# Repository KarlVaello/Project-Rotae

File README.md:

# Project-Rotae
Bike Computer, based on arduino platform. This project involves hardware, software and project design.

TASK LIST
- [ ] Hardware - Peripherals board designs
- [ ] Peripherals - Code
- [ ] Peripherals - Document proces of bluetooth configuration
- [ ] Peripherals - Shut down peripherial power via detection bluetooth unconnected
- [ ] UI - Tactile
- [ ] Hardware - batteries
- [ ] GPS general functions
- [ ] GPS location stop detection (Time stops)
- [ ] SD, save time, gps track, and data

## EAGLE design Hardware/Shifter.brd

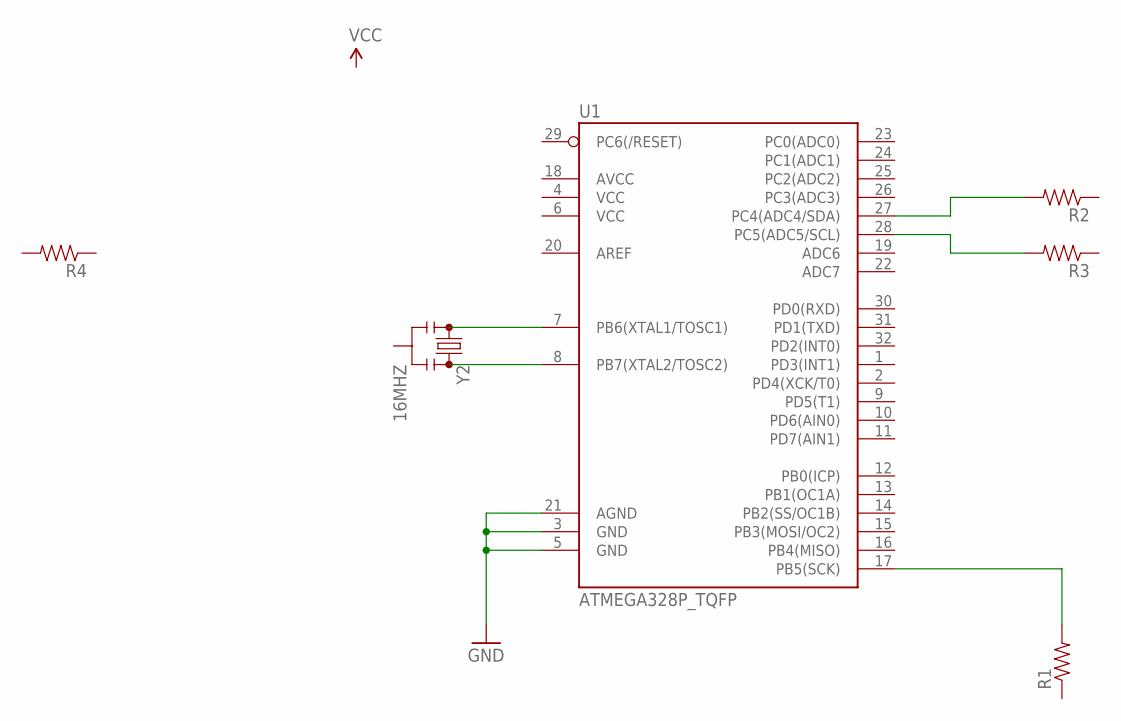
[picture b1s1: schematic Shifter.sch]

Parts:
R1, R2, R3, R4: RESISTOR0805-RES; 0805
U1: ATMEGA328P_TQFP; TQFP32-08
Y2: 16MHZ; RESONATOR-SMD

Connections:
GND: U1.3 (GND), U1.5 (GND), U1.21 (AGND)
unnamed: R1.2, U1.17 (PB5(SCK))
unnamed: R3.2, U1.28 (PC5(ADC5/SCL))
unnamed: R2.2, U1.27 (PC4(ADC4/SDA))
unnamed: U1.7 (PB6(XTAL1/TOSC1)), Y2.1
unnamed: U1.8 (PB7(XTAL2/TOSC2)), Y2.3

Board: 2 copper layers, 6 parts (0 on the bottom side), 6 nets, no tracks yet.

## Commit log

2016-09-13 initial commit
    initial commit
2016-09-14 License file
    Added GNUv3 license file (LICENSE.md).
2016-09-14 License file modifications.
    License file modifications. Added license to Arduino (.ino,.h,.cpp)
    project files.
2016-09-14 Variables added to Configuration.h
    New variables added to Configuration.h, to control baudrate
2016-09-14 Changes on gitignore
    Changes on gitignore
2016-09-14 Changes Folders and names
    Changes Folders and names
2016-09-14 Folders moved
    Folders moved
2016-09-14 Deleted empty and old folders
    Deleted empty and old folders
2016-09-14 Initial commit Ratae Lib
    Initia commit Ratae Lib
    Unstable!!
2016-09-14 Added new classes
    Added new classes
    Display (cpp,h)
    LiveData (cpp,h)
2016-09-15 Added new classes on Rotae Skech
    Added PeripheralCommunication
2016-09-16 Added new classes and New Arduino Skech Speedometer
    Added PeripheralCommunication
    Added Chrono
    New Arduino Skech Speedometer
2016-09-16 Speedometer works
    Speedometer values are read by Rota by serial. And they are printing on
    the display.
2016-09-16 Added some code documentation
    Added some code documentation
2016-09-16 Solved merge conflicts
    Stable
2016-09-16 Rotae.ino update
    Rotae.ino update
2016-09-16 PheriperialCommunication update
    PheriperialCommunication update
2016-09-18 Added two arduino skeches
    This codes are useful to config arduino bluethoot
2016-09-18 Revert "Added two arduino skeches"
    This reverts commit 8cfaad6d9909c699cfa0ff7ef3b451d31ba78c09.
2016-09-18 New folders
    Added Libraries folders -> Contains libraries needed
    Added Guides folders -> Guides
2016-09-19 More libraries and guides
    More libraries and guides
2016-09-19 Added some Icons, LiveData class changes
    Added icons to display.
    LivaData class changes, now it have a Chrono data
2016-09-20 Reading Incoming data guide example
    Reading Incoming data guide example
    byte by byte
2016-09-20 Rotate.ino changes
    Rotate.ino changes
2016-09-23 New LCD support (NOT WORKING)
    New LCD support (NOT WORKING)
2018-01-16 updt

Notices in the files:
parts and their libraries:
SparkFun-DigitalIC: Licensing: Creative Commons ShareAlike 4.0 International - https://creativecommons.org/licenses/by-sa/4.0
